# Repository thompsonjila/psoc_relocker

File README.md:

# psoc_relocker
PSoC-based PID Relocker with GUI

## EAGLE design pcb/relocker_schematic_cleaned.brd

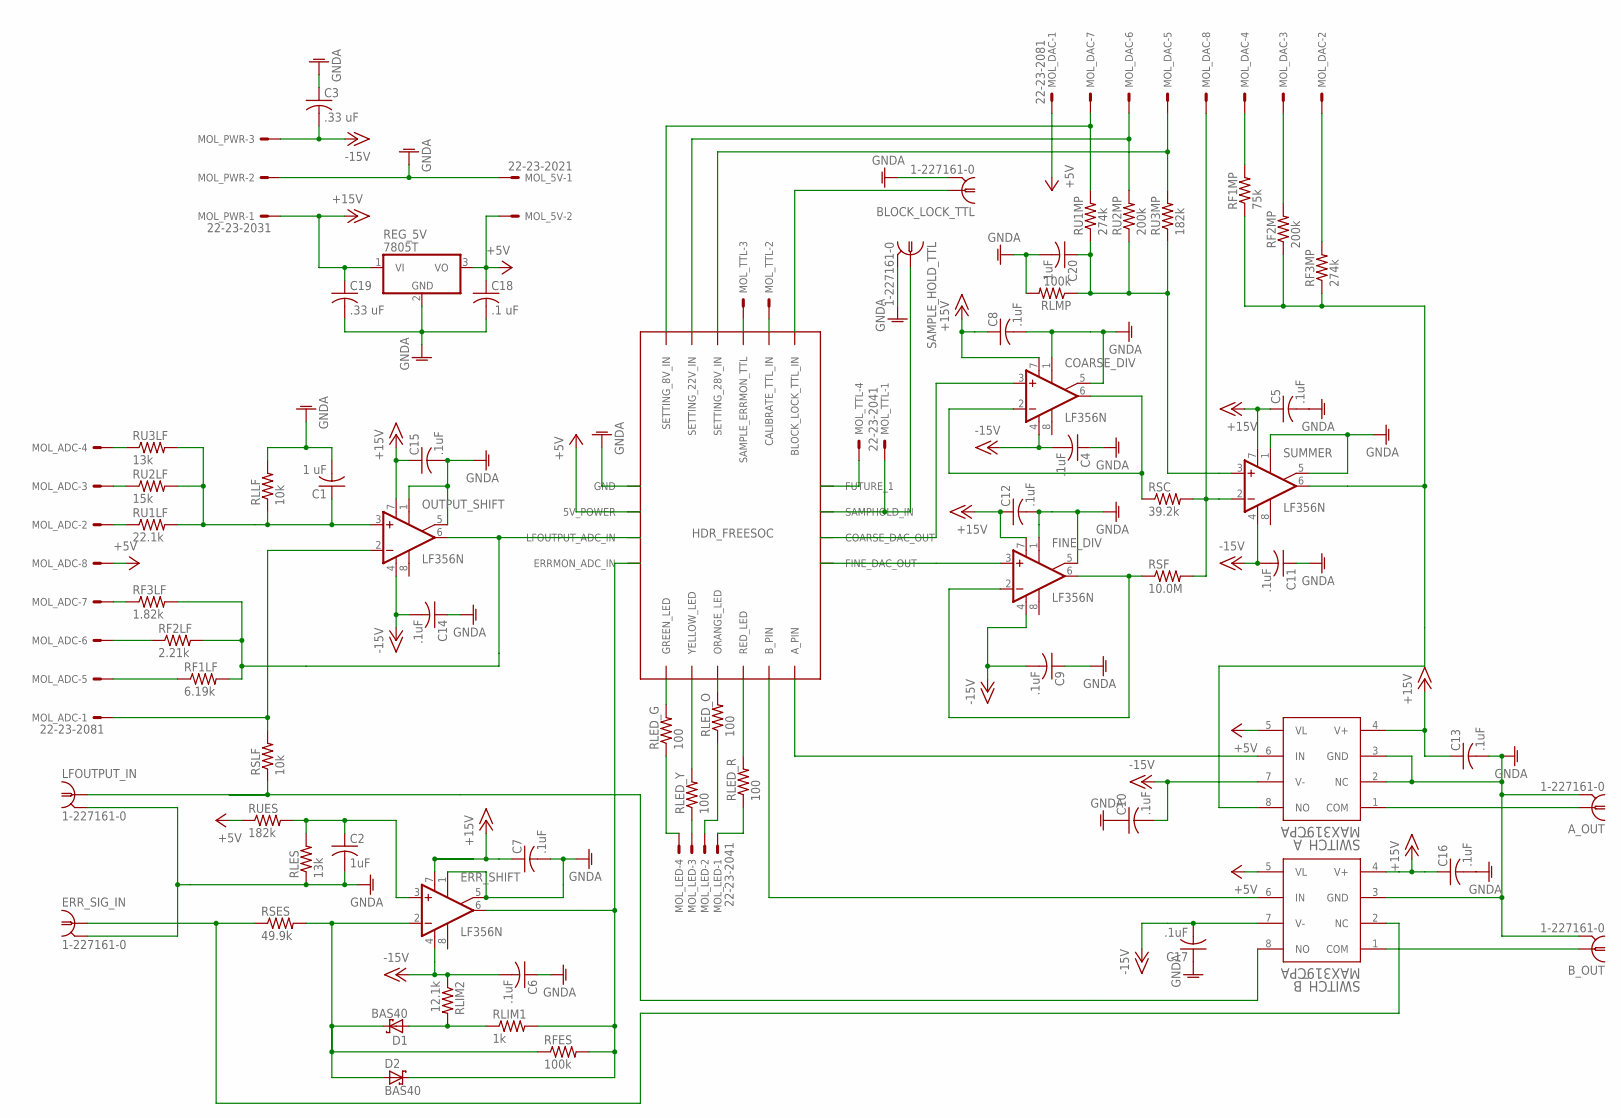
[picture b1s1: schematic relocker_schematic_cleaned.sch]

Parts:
A_OUT: 1-227161-0; AMP_227161
BLOCK_LOCK_TTL: 1-227161-0; AMP_227161
B_OUT: 1-227161-0; AMP_227161
C1: 1 uF; C0805
C2, C20: 1uF; C0805
C3, C19: .33 uF; C0805
C4, C5, C6, C7, C8, C9, C10, C11, C12, C13, C14, C15, C16, C17: .1uF; C0805
C18: .1 uF; C0805
COARSE_DIV: LF356N; DIL08
D1, D2: BAS40; SOT23
ERR_SHIFT: LF356N; DIL08
ERR_SIG_IN: 1-227161-0; AMP_227161
FINE_DIV: LF356N; DIL08
HDR_FREESOC: FREESOC2_BREAKOUT
LFOUTPUT_IN: 1-227161-0; AMP_227161
MOL_5V: 22-23-2021
MOL_ADC: 22-23-2081
MOL_DAC: 22-23-2081
MOL_LED: 22-23-2041
MOL_PWR: 22-23-2031
MOL_TTL: 22-23-2041
OUTPUT_SHIFT: LF356N; DIL08
REG_5V: 7805T; TO220H
RF1LF: 6.19k; R0805
RF1MP: 75k; R0805
RF2LF: 2.21k; R0805
RF2MP: 200k; R0805
RF3LF: 1.82k; R0805
RF3MP: 274k; R0805
RFES: 100k; R0805
RLED_G: 100; R0805
RLED_O: 100; R0805
RLED_R: 100; R0805
RLED_Y: 100; R0805
RLES: 13k; R0805
RLIM1: 1k; R0805
RLIM2: 12.1k; R0805
RLLF: 10k; R0805
RLMP: 100k; R0805
RSC: 39.2k; R0805
RSES: 49.9k; R0805
RSF: 10.0M; R0805
RSLF: 10k; R0805
RU1LF: 22.1k; R0805
RU1MP: 274k; R0805
RU2LF: 15k; R0805
RU2MP: 200k; R0805
RU3LF: 13k; R0805
RU3MP: 182k; R0805
RUES: 182k; R0805
SAMPLE_HOLD_TTL: 1-227161-0; AMP_227161
SUMMER: LF356N; DIL08
SWITCH_A: MAX319CPA; 21-0043D_8
SWITCH_B: MAX319CPA; 21-0043D_8

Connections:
+5V: C18.1, HDR_FREESOC.1 (5V_POWER), MOL_5V.2, MOL_ADC.8, MOL_DAC.1, REG_5V.3 (VO), RUES.1, SWITCH_A.5 (VL), SWITCH_B.5 (VL)
+15V: C5.1, C7.1, C8.1, C12.1, C13.1, C15.1, C16.1, C19.1, COARSE_DIV.7 (V+), ERR_SHIFT.7 (V+), FINE_DIV.7 (V+), MOL_PWR.1, OUTPUT_SHIFT.7 (V+), REG_5V.1 (VI), SUMMER.7 (V+), SWITCH_A.4 (V+), SWITCH_B.4 (V+)
-15V: C3.2, C4.2, C6.2, C9.2, C10.2, C11.2, C14.2, C17.2, COARSE_DIV.4 (V-), ERR_SHIFT.4 (V-), FINE_DIV.4 (V-), MOL_PWR.3, OUTPUT_SHIFT.4 (V-), RLIM2.1, SUMMER.4 (V-), SWITCH_A.7 (V-), SWITCH_B.7 (V-)
GNDA: A_OUT.2, BLOCK_LOCK_TTL.2, B_OUT.2, C1.2, C2.2, C3.1, C4.1, C5.2, C6.1, C7.2, C8.2, C9.1, C10.1, C11.1, C12.2, C13.2, C14.1, C15.2, C16.2, C17.1, C18.2, C19.2, C20.2, COARSE_DIV.1 (ON1), COARSE_DIV.5 (ON2), ERR_SHIFT.1 (ON1), ERR_SHIFT.5 (ON2), ERR_SIG_IN.2, FINE_DIV.1 (ON1), FINE_DIV.5 (ON2), HDR_FREESOC.2 (GND), LFOUTPUT_IN.2, MOL_5V.1, MOL_PWR.2, OUTPUT_SHIFT.1 (ON1), OUTPUT_SHIFT.5 (ON2), REG_5V.2 (GND), RLES.1, RLLF.2, RLMP.2, SAMPLE_HOLD_TTL.2, SUMMER.1 (ON1), SUMMER.5 (ON2), SWITCH_A.2 (NC), SWITCH_A.3 (GND), SWITCH_B.3 (GND)
unnamed: COARSE_DIV.3 (+IN), HDR_FREESOC.10 (COARSE_DAC_OUT)
unnamed: COARSE_DIV.2 (-IN), COARSE_DIV.6 (OUT), RSC.1
unnamed: MOL_DAC.4, RF1MP.2
unnamed: FINE_DIV.3 (+IN), HDR_FREESOC.11 (FINE_DAC_OUT)
unnamed: BLOCK_LOCK_TTL.1, HDR_FREESOC.12 (BLOCK_LOCK_TTL_IN)
unnamed: HDR_FREESOC.17 (RED_LED), RLED_R.2
unnamed: HDR_FREESOC.18 (ORANGE_LED), RLED_O.2
unnamed: HDR_FREESOC.19 (YELLOW_LED), RLED_Y.2
unnamed: HDR_FREESOC.20 (GREEN_LED), RLED_G.2
unnamed: MOL_LED.4, RLED_G.1
unnamed: MOL_LED.3, RLED_Y.1
unnamed: MOL_LED.2, RLED_O.1
unnamed: MOL_LED.1, RLED_R.1
unnamed: A_OUT.1, SWITCH_A.1 (COM)
unnamed: RF1MP.1, RF2MP.1, RF3MP.1, SUMMER.6 (OUT), SWITCH_A.8 (NO)
unnamed: HDR_FREESOC.6 (A_PIN), SWITCH_A.6 (IN)
unnamed: B_OUT.1, SWITCH_B.1 (COM)
unnamed: ERR_SIG_IN.1, RSES.1, SWITCH_B.2 (NC)
unnamed: HDR_FREESOC.9 (SETTING_8V_IN), MOL_DAC.7, RU1MP.2
unnamed: HDR_FREESOC.5 (B_PIN), SWITCH_B.6 (IN)
unnamed: LFOUTPUT_IN.1, RSLF.1, SWITCH_B.8 (NO)
unnamed: HDR_FREESOC.8 (SETTING_22V_IN), MOL_DAC.6, RU2MP.2
unnamed: HDR_FREESOC.7 (SETTING_28V_IN), MOL_DAC.5, RU3MP.2
unnamed: MOL_ADC.1, OUTPUT_SHIFT.2 (-IN), RSLF.2
unnamed: MOL_DAC.8, RSC.2, RSF.2, SUMMER.2 (-IN)
unnamed: FINE_DIV.2 (-IN), FINE_DIV.6 (OUT), RSF.1
unnamed: MOL_DAC.3, RF2MP.2
unnamed: MOL_DAC.2, RF3MP.2
unnamed: C20.1, RLMP.1, RU1MP.1, RU2MP.1, RU3MP.1, SUMMER.3 (+IN)
unnamed: HDR_FREESOC.3 (LFOUTPUT_ADC_IN), OUTPUT_SHIFT.6 (OUT), RF1LF.2, RF2LF.2, RF3LF.2
unnamed: MOL_ADC.5, RF1LF.1
unnamed: MOL_ADC.6, RF2LF.1
unnamed: MOL_ADC.7, RF3LF.1
unnamed: MOL_ADC.2, RU1LF.1
unnamed: MOL_ADC.3, RU2LF.1
unnamed: MOL_ADC.4, RU3LF.1
unnamed: C1.1, OUTPUT_SHIFT.3 (+IN), RLLF.1, RU1LF.2, RU2LF.2, RU3LF.2
unnamed: D1.3 (C), D2.1 (A), ERR_SHIFT.2 (-IN), RFES.1, RSES.2
unnamed: C2.1, ERR_SHIFT.3 (+IN), RLES.2, RUES.2
unnamed: D2.3 (C), ERR_SHIFT.6 (OUT), HDR_FREESOC.4 (ERRMON_ADC_IN), RFES.2, RLIM1.2
unnamed: HDR_FREESOC.16 (FUTURE_1), MOL_TTL.4
unnamed: HDR_FREESOC.13 (SAMPHOLD_IN), MOL_TTL.1, SAMPLE_HOLD_TTL.1
unnamed: HDR_FREESOC.14 (CALIBRATE_TTL_IN), MOL_TTL.2
unnamed: HDR_FREESOC.15 (SAMPLE_ERRMON_TTL), MOL_TTL.3
unnamed: D1.1 (A), RLIM1.1, RLIM2.2

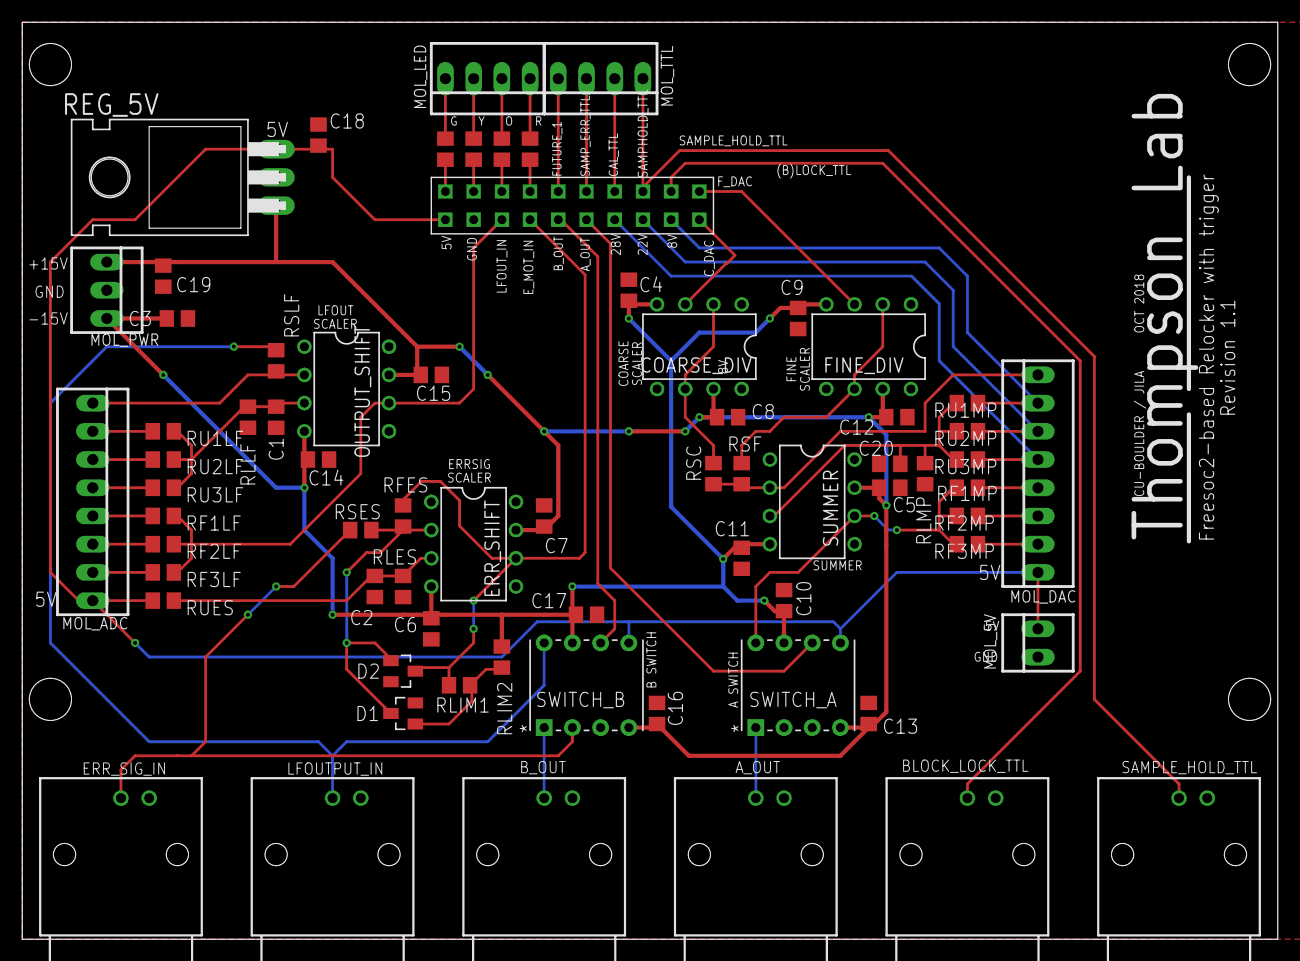
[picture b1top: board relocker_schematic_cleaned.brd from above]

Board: 2 copper layers, 113.0 x 82.5 mm, 70 parts (0 on the bottom side), 49 nets.

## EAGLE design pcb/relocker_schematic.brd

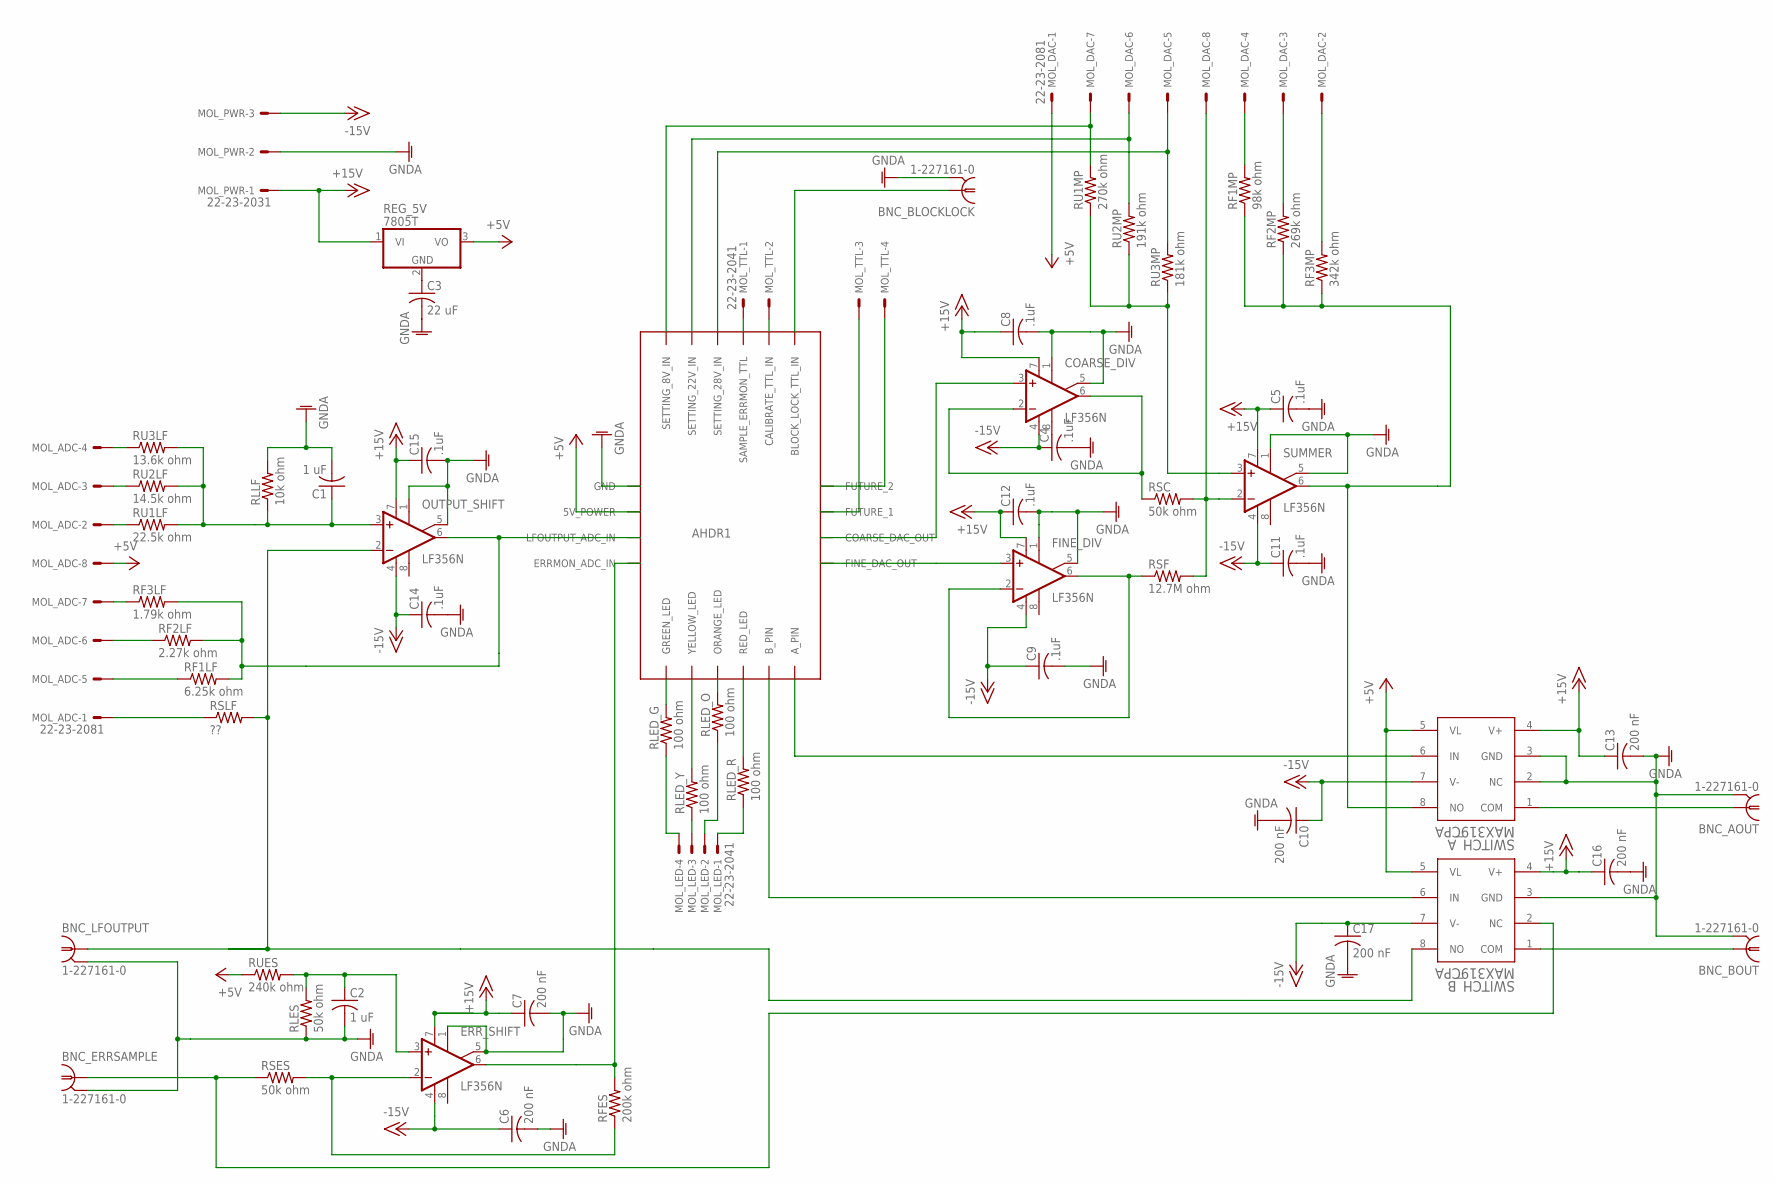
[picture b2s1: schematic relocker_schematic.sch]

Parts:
AHDR1: FREESOC2_BREAKOUT
BNC_AOUT: 1-227161-0; AMP_227161
BNC_BLOCKLOCK: 1-227161-0; AMP_227161
BNC_BOUT: 1-227161-0; AMP_227161
BNC_ERRSAMPLE: 1-227161-0; AMP_227161
BNC_LFOUTPUT: 1-227161-0; AMP_227161
C1, C2: 1 uF; C0805
C3: 22 uF; C0805
C4, C5, C8, C9, C11, C12, C14, C15: .1uF; C0805
C6, C7, C10, C13, C16, C17: 200 nF; C0805
COARSE_DIV: LF356N; DIL08
ERR_SHIFT: LF356N; DIL08
FINE_DIV: LF356N; DIL08
MOL_ADC: 22-23-2081
MOL_DAC: 22-23-2081
MOL_LED: 22-23-2041
MOL_PWR: 22-23-2031
MOL_TTL: 22-23-2041
OUTPUT_SHIFT: LF356N; DIL08
REG_5V: 7805T; TO220H
RF1LF: 6.25k ohm; R0805
RF1MP: 98k ohm; R0805
RF2LF: 2.27k ohm; R0805
RF2MP: 269k ohm; R0805
RF3LF: 1.79k ohm; R0805
RF3MP: 342k ohm; R0805
RFES: 200k ohm; R0805
RLED_G: 100 ohm; R0805
RLED_O: 100 ohm; R0805
RLED_R: 100 ohm; R0805
RLED_Y: 100 ohm; R0805
RLES: 50k ohm; R0805
RLLF: 10k ohm; R0805
RSC: 50k ohm; R0805
RSES: 50k ohm; R0805
RSF: 12.7M ohm; R0805
RSLF: ??; R0805
RU1LF: 22.5k ohm; R0805
RU1MP: 270k ohm; R0805
RU2LF: 14.5k ohm; R0805
RU2MP: 191k ohm; R0805
RU3LF: 13.6k ohm; R0805
RU3MP: 181k ohm; R0805
RUES: 240k ohm; R0805
SUMMER: LF356N; DIL08
SWITCH_A: MAX319CPA; 21-0043D_8
SWITCH_B: MAX319CPA; 21-0043D_8

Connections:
+5V: AHDR1.1 (5V_POWER), MOL_ADC.8, MOL_DAC.1, REG_5V.3 (VO), RUES.1, SWITCH_A.5 (VL), SWITCH_B.5 (VL)
+15V: C5.1, C7.1, C8.1, C12.1, C13.1, C15.1, C16.1, COARSE_DIV.7 (V+), ERR_SHIFT.7 (V+), FINE_DIV.7 (V+), MOL_PWR.1, OUTPUT_SHIFT.7 (V+), REG_5V.1 (VI), SUMMER.7 (V+), SWITCH_A.4 (V+), SWITCH_B.4 (V+)
-15V: C4.1, C6.1, C9.1, C10.1, C11.1, C14.1, C17.1, COARSE_DIV.4 (V-), ERR_SHIFT.4 (V-), FINE_DIV.4 (V-), MOL_PWR.3, OUTPUT_SHIFT.4 (V-), SUMMER.4 (V-), SWITCH_A.7 (V-), SWITCH_B.7 (V-)
GNDA: AHDR1.2 (GND), BNC_AOUT.2, BNC_BLOCKLOCK.2, BNC_BOUT.2, BNC_ERRSAMPLE.2, BNC_LFOUTPUT.2, C1.2, C2.2, C3.1, C3.2, C4.2, C5.2, C6.2, C7.2, C8.2, C9.2, C10.2, C11.2, C12.2, C13.2, C14.2, C15.2, C16.2, C17.2, COARSE_DIV.1 (ON1), COARSE_DIV.5 (ON2), ERR_SHIFT.1 (ON1), ERR_SHIFT.5 (ON2), FINE_DIV.1 (ON1), FINE_DIV.5 (ON2), MOL_PWR.2, OUTPUT_SHIFT.1 (ON1), OUTPUT_SHIFT.5 (ON2), REG_5V.2 (GND), RLES.1, RLLF.2, SUMMER.1 (ON1), SUMMER.5 (ON2), SWITCH_A.2 (NC), SWITCH_A.3 (GND), SWITCH_B.3 (GND)
unnamed: AHDR1.10 (COARSE_DAC_OUT), COARSE_DIV.3 (+IN)
unnamed: COARSE_DIV.2 (-IN), COARSE_DIV.6 (OUT), RSC.1
unnamed: MOL_DAC.4, RF1MP.2
unnamed: AHDR1.11 (FINE_DAC_OUT), FINE_DIV.3 (+IN)
unnamed: AHDR1.12 (BLOCK_LOCK_TTL_IN), BNC_BLOCKLOCK.1
unnamed: AHDR1.17 (RED_LED), RLED_R.2
unnamed: AHDR1.18 (ORANGE_LED), RLED_O.2
unnamed: AHDR1.19 (YELLOW_LED), RLED_Y.2
unnamed: AHDR1.20 (GREEN_LED), RLED_G.2
unnamed: MOL_LED.4, RLED_G.1
unnamed: MOL_LED.3, RLED_Y.1
unnamed: MOL_LED.2, RLED_O.1
unnamed: MOL_LED.1, RLED_R.1
unnamed: BNC_AOUT.1, SWITCH_A.1 (COM)
unnamed: RF1MP.1, RF2MP.1, RF3MP.1, SUMMER.6 (OUT), SWITCH_A.8 (NO)
unnamed: AHDR1.6 (A_PIN), SWITCH_A.6 (IN)
unnamed: BNC_BOUT.1, SWITCH_B.1 (COM)
unnamed: BNC_ERRSAMPLE.1, RSES.1, SWITCH_B.2 (NC)
unnamed: AHDR1.9 (SETTING_8V_IN), MOL_DAC.7, RU1MP.2
unnamed: AHDR1.5 (B_PIN), SWITCH_B.6 (IN)
unnamed: BNC_LFOUTPUT.1, OUTPUT_SHIFT.2 (-IN), RSLF.2, SWITCH_B.8 (NO)
unnamed: AHDR1.8 (SETTING_22V_IN), MOL_DAC.6, RU2MP.2
unnamed: AHDR1.7 (SETTING_28V_IN), MOL_DAC.5, RU3MP.2
unnamed: AHDR1.3 (LFOUTPUT_ADC_IN), OUTPUT_SHIFT.6 (OUT), RF1LF.2, RF2LF.2, RF3LF.2
unnamed: MOL_DAC.8, RSC.2, RSF.2, SUMMER.2 (-IN)
unnamed: FINE_DIV.2 (-IN), FINE_DIV.6 (OUT), RSF.1
unnamed: MOL_DAC.3, RF2MP.2
unnamed: MOL_DAC.2, RF3MP.2
unnamed: RU1MP.1, RU2MP.1, RU3MP.1, SUMMER.3 (+IN)
unnamed: MOL_ADC.1, RSLF.1
unnamed: MOL_ADC.5, RF1LF.1
unnamed: MOL_ADC.6, RF2LF.1
unnamed: MOL_ADC.7, RF3LF.1
unnamed: MOL_ADC.2, RU1LF.1
unnamed: MOL_ADC.3, RU2LF.1
unnamed: MOL_ADC.4, RU3LF.1
unnamed: C1.1, OUTPUT_SHIFT.3 (+IN), RLLF.1, RU1LF.2, RU2LF.2, RU3LF.2
unnamed: ERR_SHIFT.2 (-IN), RFES.1, RSES.2
unnamed: C2.1, ERR_SHIFT.3 (+IN), RLES.2, RUES.2
unnamed: AHDR1.4 (ERRMON_ADC_IN), ERR_SHIFT.6 (OUT), RFES.2
unnamed: AHDR1.15 (FUTURE_1), MOL_TTL.3
unnamed: AHDR1.16 (FUTURE_2), MOL_TTL.4
unnamed: AHDR1.14 (CALIBRATE_TTL_IN), MOL_TTL.2
unnamed: AHDR1.13 (SAMPLE_ERRMON_TTL), MOL_TTL.1

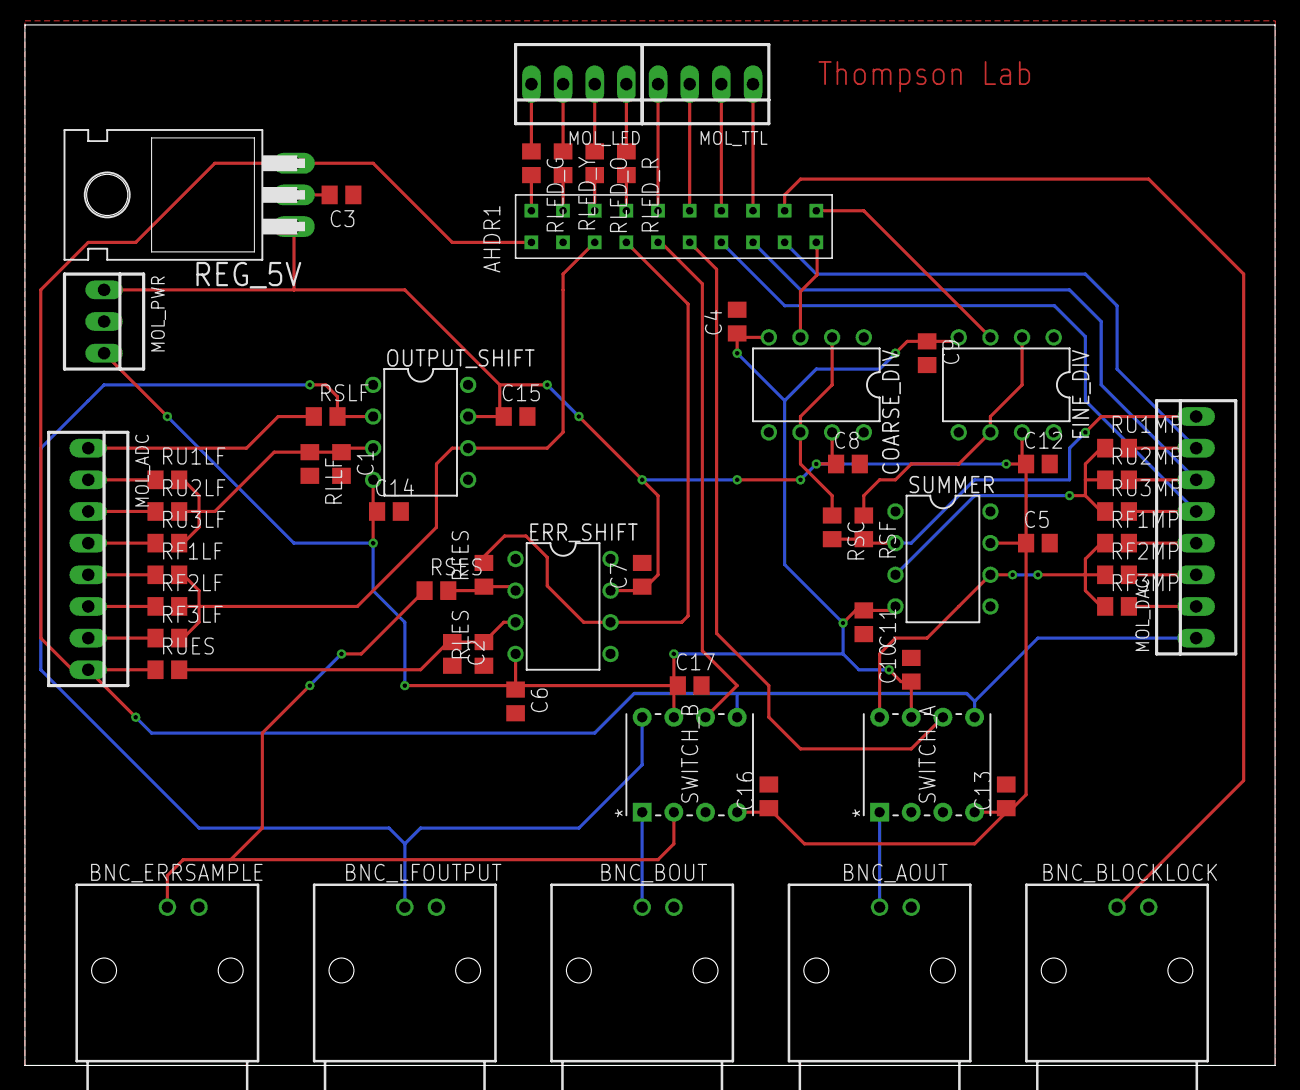
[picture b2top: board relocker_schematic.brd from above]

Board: 2 copper layers, 100.3 x 83.5 mm, 60 parts (0 on the bottom side), 48 nets.

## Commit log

2019-08-15 initial population
2019-09-06 Improved plotting
2019-09-17 add psoc files, documentation
2021-01-19 latest updates
